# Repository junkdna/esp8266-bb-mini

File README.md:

# Mini BaseBoard for the ESP8266

## Firmware
The board can be used with the [ESP8266 Sensor](https://github.com/junkdna/esp8266-sensor-firmware) firmware.

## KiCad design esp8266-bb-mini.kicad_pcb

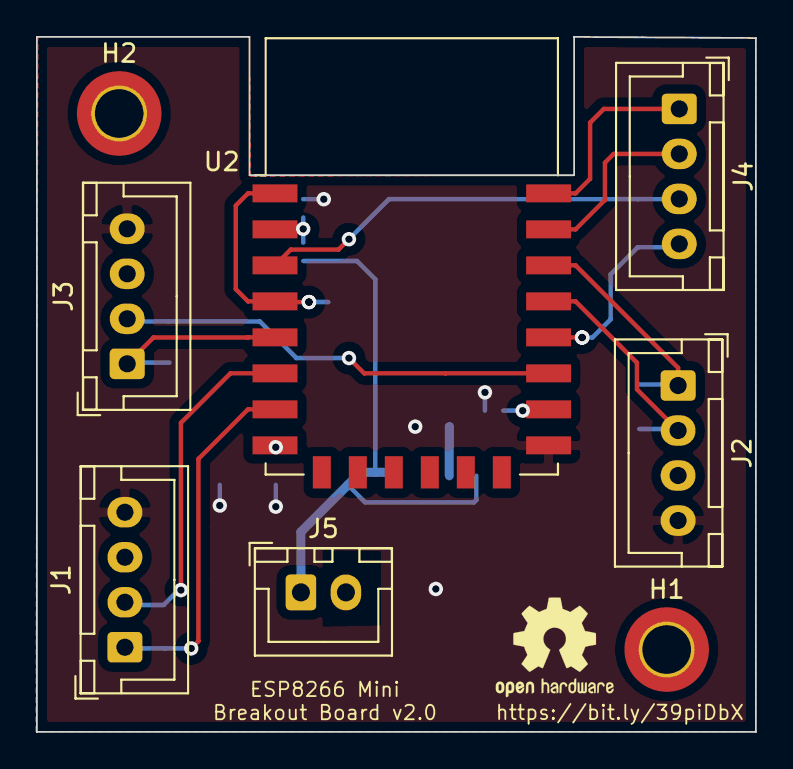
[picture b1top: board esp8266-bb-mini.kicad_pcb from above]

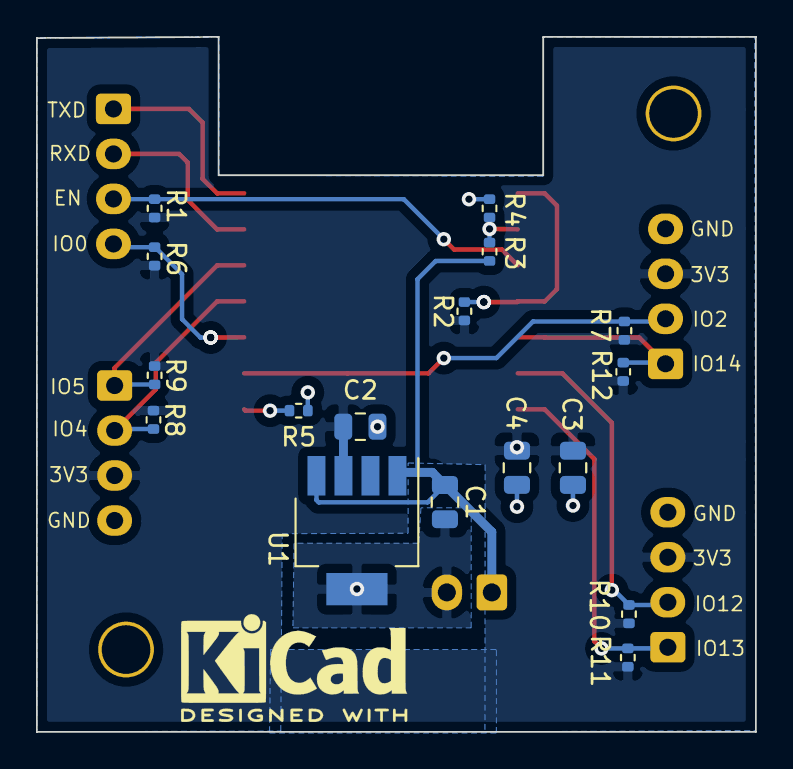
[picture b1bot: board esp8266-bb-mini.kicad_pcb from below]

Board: 2 copper layers, 39.9 x 38.6 mm, 25 parts (17 on the bottom side), 16 nets.

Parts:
C1, C2, C3: 10uF; C_0805_2012Metric
C4: 100nF; C_0805_2012Metric
H1, H2: MountingHole; MountingHole_2.7mm_M2.5_DIN965_Pad_TopOnly
J1, J2, J3, J4: Conn_01x04_Male; JST_XH_B4B-XH-A_1x04_P2.50mm_Vertical
J5: Conn_01x02_Male; JST_XH_B2B-XH-A_1x02_P2.50mm_Vertical
R1, R2, R5, R6, R7, R8, R9, R10, R11, R12: 10k; R_0402_1005Metric
R3: 47k; R_0402_1005Metric
R4: 9k; R_0402_1005Metric
U1: LP38693MP-3.3; SOT-223-5
U2: ESP-12F; ESP-12E

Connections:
+3V3: C2.2, C3.1, C4.2, J1.3, J2.3, J3.3, R1.1, R2.1, R6.1, R7.1, R8.1, R9.1, R10.1, R11.1, R12.1, U1.3, U2.8
+BATT: C1.1, J5.1, R3.1, U1.1, U1.4
-BATT: C1.2, C2.1, C3.2, C4.1, J1.4, J2.4, J3.4, J5.2, R4.2, R5.2, U1.5, U2.15
/ADC_IN: R3.2, R4.1, U2.2
/EXT_EN: J4.3, R1.2, U2.3
/EXT_GPIO0: J4.4, R6.2, U2.18
/EXT_GPIO2: J3.2, R7.2, U2.17
/EXT_GPIO4: J2.2, R8.2, U2.19
/EXT_GPIO5: J2.1, R9.2, U2.20
/EXT_GPIO12: J1.2, R10.2, U2.6
/EXT_GPIO13: J1.1, R11.2, U2.7
/EXT_GPIO14: J3.1, R12.2, U2.5
/EXT_GPIO15: R5.1, U2.16
/EXT_RXD: J4.2, U2.21
/EXT_TXD: J4.1, U2.22
/nRST: R2.2, U2.1, U2.4

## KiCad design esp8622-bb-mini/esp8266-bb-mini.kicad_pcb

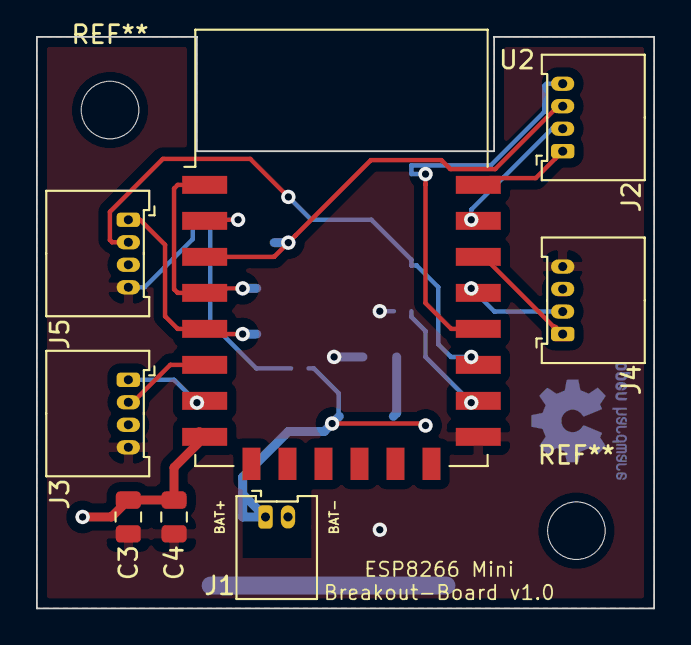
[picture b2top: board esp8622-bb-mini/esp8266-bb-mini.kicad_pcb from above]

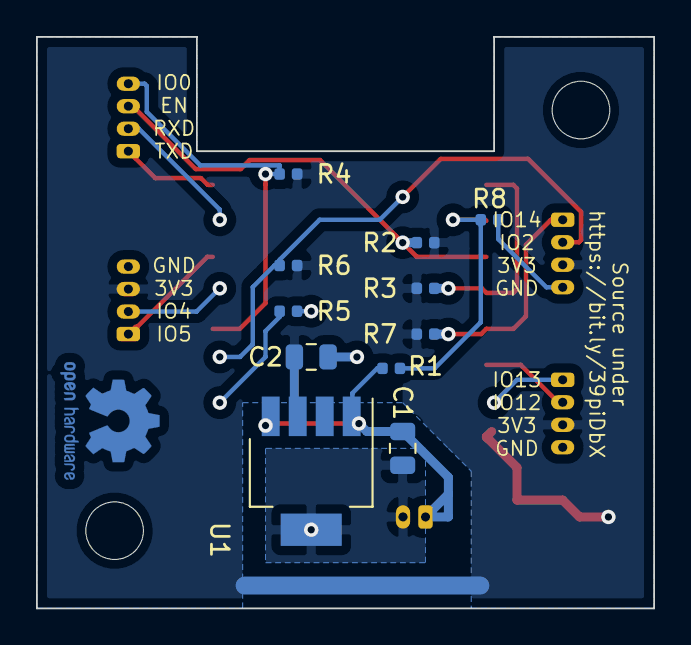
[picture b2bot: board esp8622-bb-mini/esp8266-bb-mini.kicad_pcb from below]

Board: 2 copper layers, 34.3 x 31.8 mm, 19 parts (11 on the bottom side), 16 nets.

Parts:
C1, C2, C3: 10uF; C_0805_2012Metric
C4: 100nF; C_0805_2012Metric
J1: Conn_01x02_Male; Molex_PicoBlade_53048-0210_1x02_P1.25mm_Horizontal
J2, J3, J4, J5: Conn_01x04_Male; Molex_PicoBlade_53048-0410_1x04_P1.25mm_Horizontal
R1: 47k; R_0402_1005Metric
R2, R3, R4, R5, R6, R7: 10k; R_0402_1005Metric
R8: 9k; R_0402_1005Metric
U1: LP38693MP-3.3; SOT-223-5
U2: ESP-12F; ESP-12E

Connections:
+3V3: C2.2, C3.1, C4.2, J3.3, J4.3, J5.3, R2.1, R3.1, R4.2, R6.1, R7.1, U1.3, U2.8
+BATT: C1.1, J1.1, R1.1, U1.1, U1.4
-BATT: C1.2, C2.1, C3.2, C4.1, J1.2, J3.4, J4.4, J5.4, R5.2, R8.2, U1.5, U2.15
/ADC_IN: R1.2, R8.1, U2.2
/EXT_EN: J2.3, R2.2, U2.3
/EXT_GPIO0: J2.4, R4.1, U2.18
/EXT_GPIO2: J5.2, R6.2, U2.17
/EXT_GPIO4: J4.2, U2.19
/EXT_GPIO5: J4.1, U2.20
/EXT_GPIO12: J3.2, U2.6
/EXT_GPIO13: J3.1, U2.7
/EXT_GPIO14: J5.1, R7.2, U2.5
/EXT_GPIO15: R5.1, U2.16
/EXT_RXD: J2.2, U2.21
/EXT_TXD: J2.1, U2.22
/nRST: R3.2, U2.1, U2.4

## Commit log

2020-11-29 initial schematic and layout
2020-11-29 update layout
    - add mounting holes; in order to place them diagonally move the connectors around a little
    - add informative texts
2020-11-30 sch: add power flags
2020-11-30 add CI
2020-12-01 sch: add voltage divider for battery level sensing
2020-12-01 brd: fix regression drd error
2020-12-01 brd: misc changes
    - re-add mounting holes
    - fix copper pour keepout around input connector
    - incooperate voltage divider
2020-12-01 sch/brd: add page title and revision
2020-12-01 project: adapt structure to work (better) with CI
2020-12-02 add kiplot configuration and kibot install helper
2020-12-02 update workflow
2020-12-02 ignore more temporary, generated and backup files
2020-12-02 stay on toplevel
2020-12-02 update name to use main instead of master
2020-12-02 workflow: fix task names
2020-12-02 pcb: move silk screen labels around to make them more consistent in relation to their part on the pcb
2020-12-02 imported 3d models for Molex connectors
    https://www.molex.com/molex/products/part-detail/pcb_headers/0530480210
    https://www.molex.com/molex/products/part-detail/pcb_headers/0530480410
2020-12-03 brd: add oshw logo
2020-12-03 brd: improve copper pour on gnd plane
2020-12-03 brd: improve routing for better connected copper pour on 3v3 plane
2021-01-01 new layout with bigger connectors
2021-01-01 schematic: reduce mounting holes to m2.5, change type to with pad on top
2021-01-01 add pull-ups for all gpios
2021-01-01 pcb: fix https link on silk
2021-02-19 readme: add link to firmware
